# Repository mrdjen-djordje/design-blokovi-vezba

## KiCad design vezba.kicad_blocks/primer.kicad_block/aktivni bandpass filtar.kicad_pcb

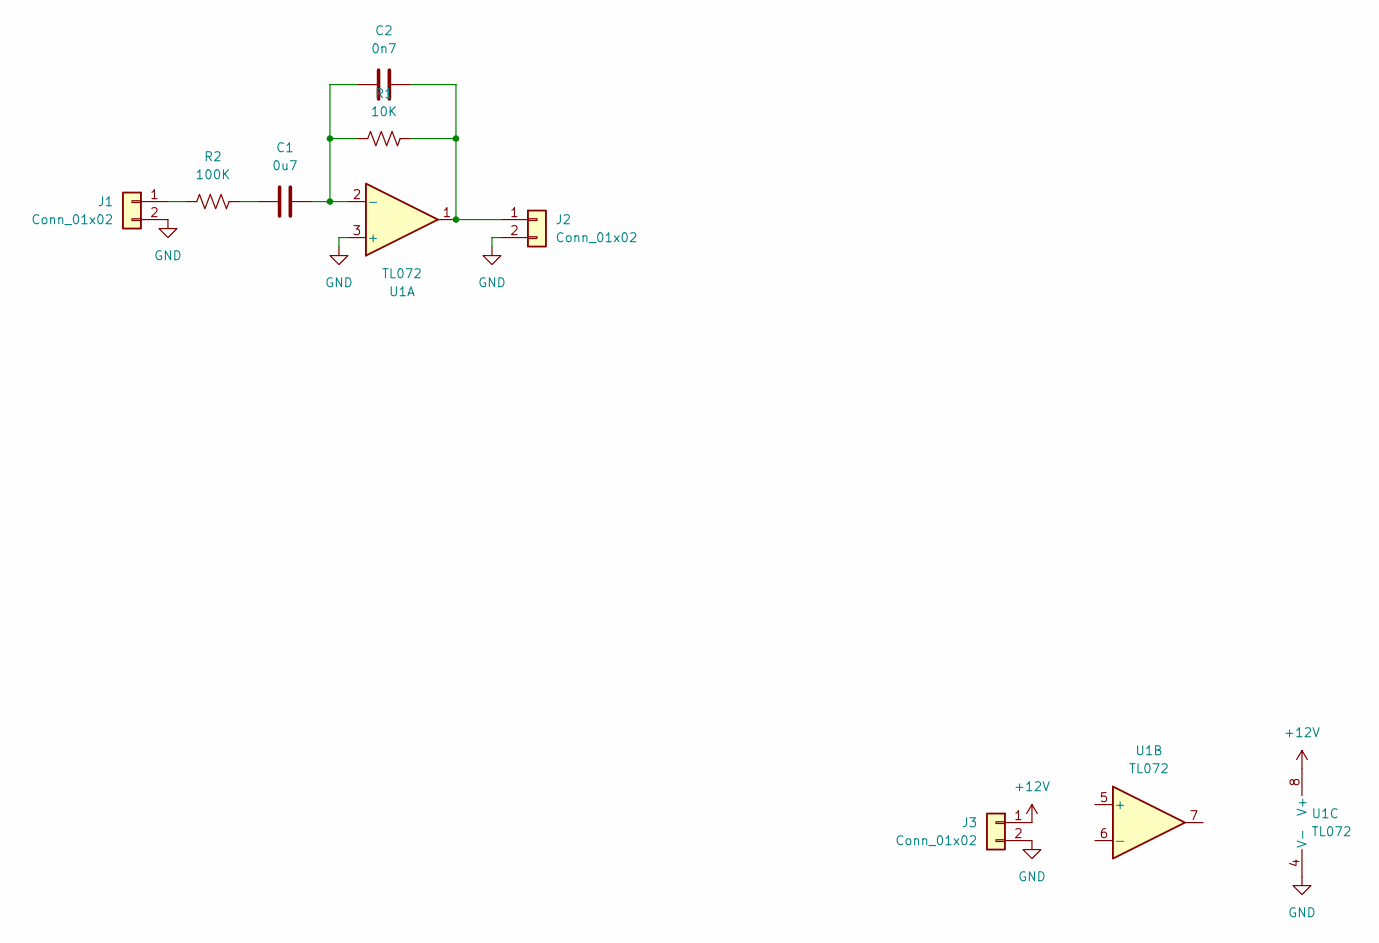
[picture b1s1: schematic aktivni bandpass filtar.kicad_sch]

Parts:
C1: 0u7; C_1206_3216Metric
C2: 0n7; C_1206_3216Metric
J1, J2, J3: Conn_01x02; PinHeader_1x02_P2.54mm_Vertical
R1: 10K; R_1206_3216Metric
R2: 100K; R_1206_3216Metric
U1: TL072; SOIC-8_5.3x6.2mm_P1.27mm

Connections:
+12V: J3.1, U1.8 (V+)
GND: J1.2, J2.2, J3.2, U1.3 (+), U1.4 (V-)
unnamed: C1.1, R2.2
unnamed: J1.1, R2.1
unnamed: C2.2, J2.1, R1.2, U1.1
unnamed: C1.2, C2.1, R1.1, U1.2 (-)

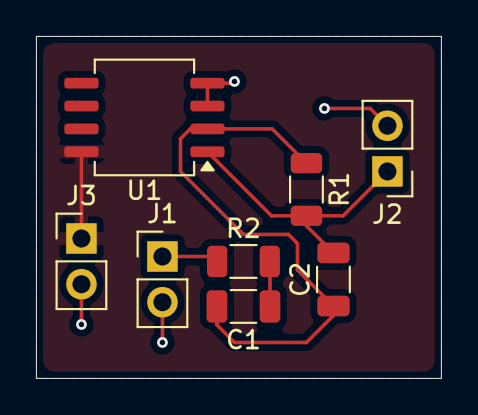
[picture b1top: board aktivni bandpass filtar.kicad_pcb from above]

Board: 2 copper layers, 22.5 x 19.0 mm, 8 parts (0 on the bottom side), 6 nets.
